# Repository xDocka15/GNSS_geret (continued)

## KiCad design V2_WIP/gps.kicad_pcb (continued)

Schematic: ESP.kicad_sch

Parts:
C2, C14, C15: 100nF; C_0603_1608Metric_Pad1.08x0.95mm_HandSolder
C3, C11, C204: 10uF; C_0603_1608Metric_Pad1.08x0.95mm_HandSolder
C201: 22uF; C_0603_1608Metric_Pad1.08x0.95mm_HandSolder
C202: 470uF; C_Elec_6.3x7.7; not fitted
C203: 1uF; C_0603_1608Metric_Pad1.08x0.95mm_HandSolder
D3, D4: M2; D_SMA
D6, D7: 1N4148W-G3-08; D_SOD-123
D201: LED; LED_D3.0mm
J202: USB4145-03-0230-C; USB4145030230C; Manufacturer_Part_Number USB4145-03-0230-C
Q1: IRLML5203; SOT-23
Q2, Q3: S8050; SOT-23-3
R2, R15: 220; R_0603_1608Metric_Pad0.98x0.95mm_HandSolder
R9, R12, R20, R203: 10k; R_0603_1608Metric_Pad0.98x0.95mm_HandSolder
R10, R16: 2k; R_0603_1608Metric_Pad0.98x0.95mm_HandSolder
R11: 200k; R_0603_1608Metric_Pad0.98x0.95mm_HandSolder
R108: 1k; R_0603_1608Metric_Pad0.98x0.95mm_HandSolder
R202: Manual rst; R_0603_1608Metric_Pad0.98x0.95mm_HandSolder; not fitted
R204, R205: 5k1; R_0603_1608Metric_Pad0.98x0.95mm_HandSolder
SW2: PTS647SN70SMTR2N LFS; SW_SPST_PTS647_Sx38
TP8: +3V3_ESP; TestPoint_Pad_D1.0mm
TP201: FLED; TestPoint_Pad_D1.0mm
TP202: LDO_VCC; TestPoint_Pad_D1.0mm
U1: ESP32-WROOM-32UE
U14: *CH340K; SSOP-10-1EP_3.9x4.9mm_P1mm_EP2.1x3.3mm
U201: RT9080-33GJ5; SOT-23-5_HandSoldering

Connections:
+3V3_ESP: C2.1, C3.1, C201.1, C202.1, C203.1, C204.1, R9.1, R108.2, R203.1, TP8.1 (1_1), U1.2 (VDD), U201.5 (VOUT); also elsewhere on the board
/CLK: U1.11 (IO26); also elsewhere on the board
/DT: U1.12 (IO27); also elsewhere on the board
/ESP/DTR: Q3.1 (E), R20.2, U14.4 (~DTR)
/ESP/D_N: J202.A7 (DN1), J202.B7 (DN2), U14.2 (UD-)
/ESP/D_P: J202.A6 (DP1), J202.B6 (DP2), U14.1 (UD+)
/ESP/IO0: D7.2 (A), U1.25 (IO0)
/ESP/IO2: R10.1, TP201.1 (1_1), U1.24 (IO2)
/ESP/IO12: U1.14 (IO12); also elsewhere on the board
/ESP/IO15: R2.1, U1.23 (IO15)
/ESP/RST: D6.2 (A), R9.2, R202.1, U1.3 (EN)
/ESP/RTS: Q2.1 (E), Q3.2 (B), U14.6 (~RTS)
/ESP/RxD0: U1.34 (RXD0/IO3), U14.9 (RXD)
/ESP/TxD0: R15.1, U1.35 (TXD0/IO1)
/ESP/VCC: C11.1, D3.1 (K), D4.1 (K), Q1.2 (S), R11.1, TP202.1 (1_1), U201.1 (VIN)
/GNSS_RxD: U1.28 (IO17); also elsewhere on the board
/GNSS_TxD: U1.27 (IO16); also elsewhere on the board
/LDO_EN: U1.9 (IO33); also elsewhere on the board
/LIGHT_SENS: U1.7 (IO35); also elsewhere on the board
/MISO: U1.31 (IO19); also elsewhere on the board
/MOSI: U1.37 (IO23); also elsewhere on the board
/Pulse: U1.13 (IO14); also elsewhere on the board
/RGB_DATA: U1.16 (IO13); also elsewhere on the board
/SCK: U1.30 (IO18); also elsewhere on the board
/SCL_3V3: U1.36 (IO22); also elsewhere on the board
/SDA_3V3: U1.33 (IO21); also elsewhere on the board
/SEL_FL: U1.26 (IO4); also elsewhere on the board
/SEL_IMU: U1.8 (IO32); also elsewhere on the board
/SW: U1.10 (IO25); also elsewhere on the board
/VBATT: Q1.3 (D); also elsewhere on the board
/VUSB: C14.1, D3.2 (A), D4.2 (A), J202.A4 (VBUS_1), J202.A9 (VBUS_2), J202.B4 (VBUS_3), J202.B9 (VBUS_4), Q1.1 (G), R12.2, U14.7 (VCC); also elsewhere on the board
GND: C2.2, C3.2, C11.2, C14.2, C15.2, C201.2, C202.2, C203.2, C204.2, D201.1 (K), J202.A1 (GND_1), J202.A8 (SBU1), J202.A12 (GND_2), J202.B1 (GND_3), J202.B8 (SBU2), J202.B12 (GND_4), J202.MH1 (MH5), J202.MH2 (MH6), J202.MH3, J202.MH4, R12.1, R202.2, R204.2, R205.1, SW2.2, U1.1 (GND), U1.15 (GND), U1.38 (GND), U1.39 (GND), U14.3 (GND), U14.11 (GND), U201.2 (GND); also elsewhere on the board
unnamed: D6.1 (K), Q2.3 (C)
unnamed: D7.1 (K), Q3.3 (C)
unnamed: D201.2 (A), R10.2
unnamed: J202.A5 (CC1), R204.1
unnamed: J202.B5 (CC2), R205.2
unnamed: Q2.2 (B), R20.1
unnamed: R2.2, R203.2, SW2.1
unnamed: R108.1, U1.29 (IO5)
unnamed: R15.2, R16.2, U14.8 (TXD)
unnamed: C15.1, R16.1, U14.10 (V3)
unnamed: R11.2, U201.3 (EN)

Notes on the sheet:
LDO_EN
ENC CLK
SEL_IMU
RTS
SCK MISO SDA SCL MOSI
ENC DT
GNSS TX
PULSE
LIGHT_SENS
RGB_DATA
SEL_FL
TP12
SW2
ENC SW
IMU_INT
GNSSRX
LED
https://www.tme.eu/cz/details/usb4145-03-0230-c/konektory-usb-a-ieee1394/gct/
MaxOut 600mA
Manual rst possible by shorting R202
Pins GPIO6 to GPIO11 are connected to the integrated SPI flash integrated on the module and are not recommended for other uses. IO5, 14, 15 are active HIGH at boot IO0, 5, 15 must be HI at boot IO2, 12 must be LO at boot

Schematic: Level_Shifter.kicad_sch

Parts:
C10: 100nF; C_0603_1608Metric_Pad1.08x0.95mm_HandSolder
R3, R4, R5, R6: 10k; R_0603_1608Metric_Pad0.98x0.95mm_HandSolder
RS1: 200k; R_0603_1608Metric_Pad0.98x0.95mm_HandSolder
U9: *TCA39306DDFR; SOT-23-8

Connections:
+3V3: R3.1, R4.1, U9.2 (VREF1); also elsewhere on the board
+5V: R5.1, R6.1, RS1.1; also elsewhere on the board
/SCL_3V3: R3.2, U9.3 (SCL1); also elsewhere on the board
/SCL_5V: R6.2, U9.6 (SCL2); also elsewhere on the board
/SDA_3V3: R4.2, U9.4 (SDA1); also elsewhere on the board
/SDA_5V: R5.2, U9.5 (SDA2); also elsewhere on the board
GND: C10.1, U9.1 (GND); also elsewhere on the board
unnamed: C10.2, RS1.2, U9.7 (VREF2), U9.8 (EN)

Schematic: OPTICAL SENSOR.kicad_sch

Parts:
C107: 100nF; C_0603_1608Metric_Pad1.08x0.95mm_HandSolder
IC1: OPT3001DNPR; SON65P200X200X65-7N-D; Mouser Part Number 595-OPT3001DNPR
R7, R8: 10k; R_0603_1608Metric_Pad0.98x0.95mm_HandSolder
TP14: OPT_INT; TestPoint_Pad_D1.0mm

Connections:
+3V3: C107.2, IC1.1 (VDD), R7.1, R8.1; also elsewhere on the board
/SCL_3V3: IC1.4 (SCL), R8.2; also elsewhere on the board
/SDA_3V3: IC1.6 (SDA), R7.2; also elsewhere on the board
GND: C107.1, IC1.2 (ADDR), IC1.3 (GND), IC1.7 (EP); also elsewhere on the board
unnamed: IC1.5 (INT), TP14.1 (1_1)

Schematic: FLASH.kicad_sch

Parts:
C101: 100nF; C_0603_1608Metric_Pad1.08x0.95mm_HandSolder
R_E101, R_E102: 10k; R_0603_1608Metric_Pad0.98x0.95mm_HandSolder
U102: W25N02KVZEIR; WSON-8-1EP_8x6mm_P1.27mm_EP3.4x4.3mm

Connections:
+3V3: C101.2, R_E101.1, R_E102.2, U102.8 (VCC); also elsewhere on the board
/MISO: U102.2 (DO(IO1)); also elsewhere on the board
/MOSI: U102.5 (DI(IO0)); also elsewhere on the board
/SCK: U102.6 (CLK); also elsewhere on the board
/SEL_FL: U102.1 (~CS); also elsewhere on the board
GND: C101.1, U102.4 (GND); also elsewhere on the board
unnamed: R_E102.1, U102.3 (IO2)
unnamed: R_E101.2, U102.7 (IO3)

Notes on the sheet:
connected to ESP or PULL UP

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
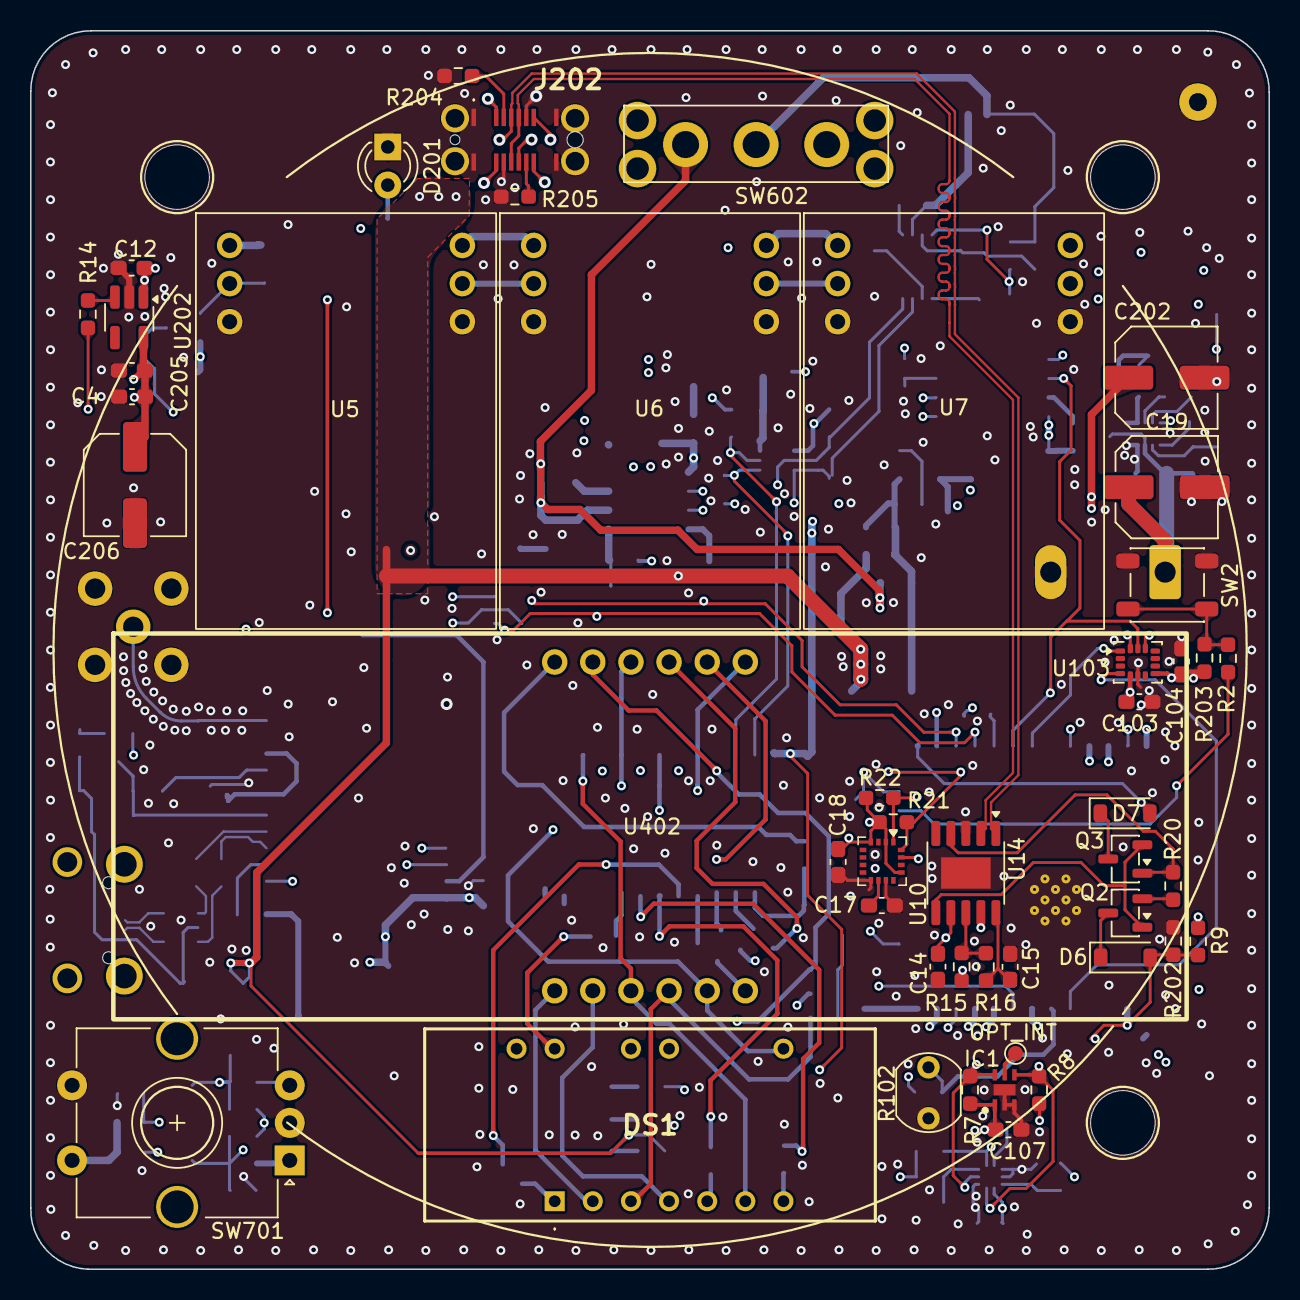
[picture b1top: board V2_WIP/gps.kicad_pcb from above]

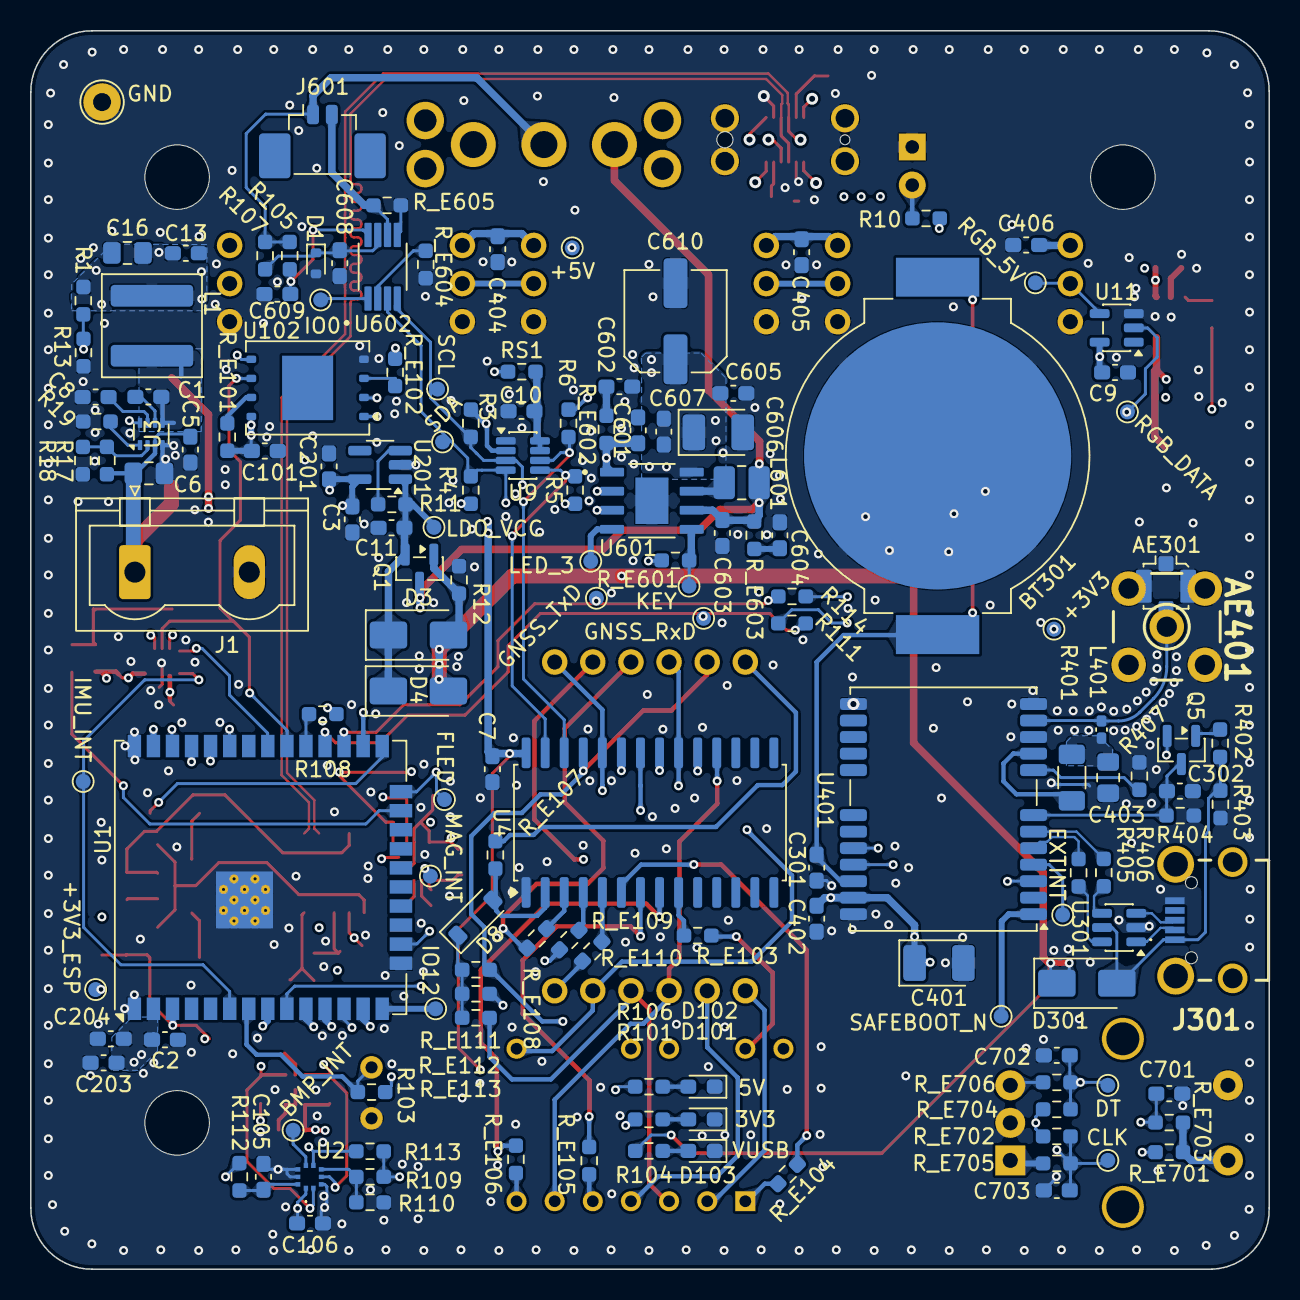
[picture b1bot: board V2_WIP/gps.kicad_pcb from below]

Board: 6 copper layers, 82.5 x 82.5 mm, 198 parts (150 on the bottom side), 129 nets.

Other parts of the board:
C607: 22u; C_0603_1608Metric_Pad1.08x0.95mm_HandSolder

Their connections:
+5V: C607.1, C607.2; also elsewhere on the board

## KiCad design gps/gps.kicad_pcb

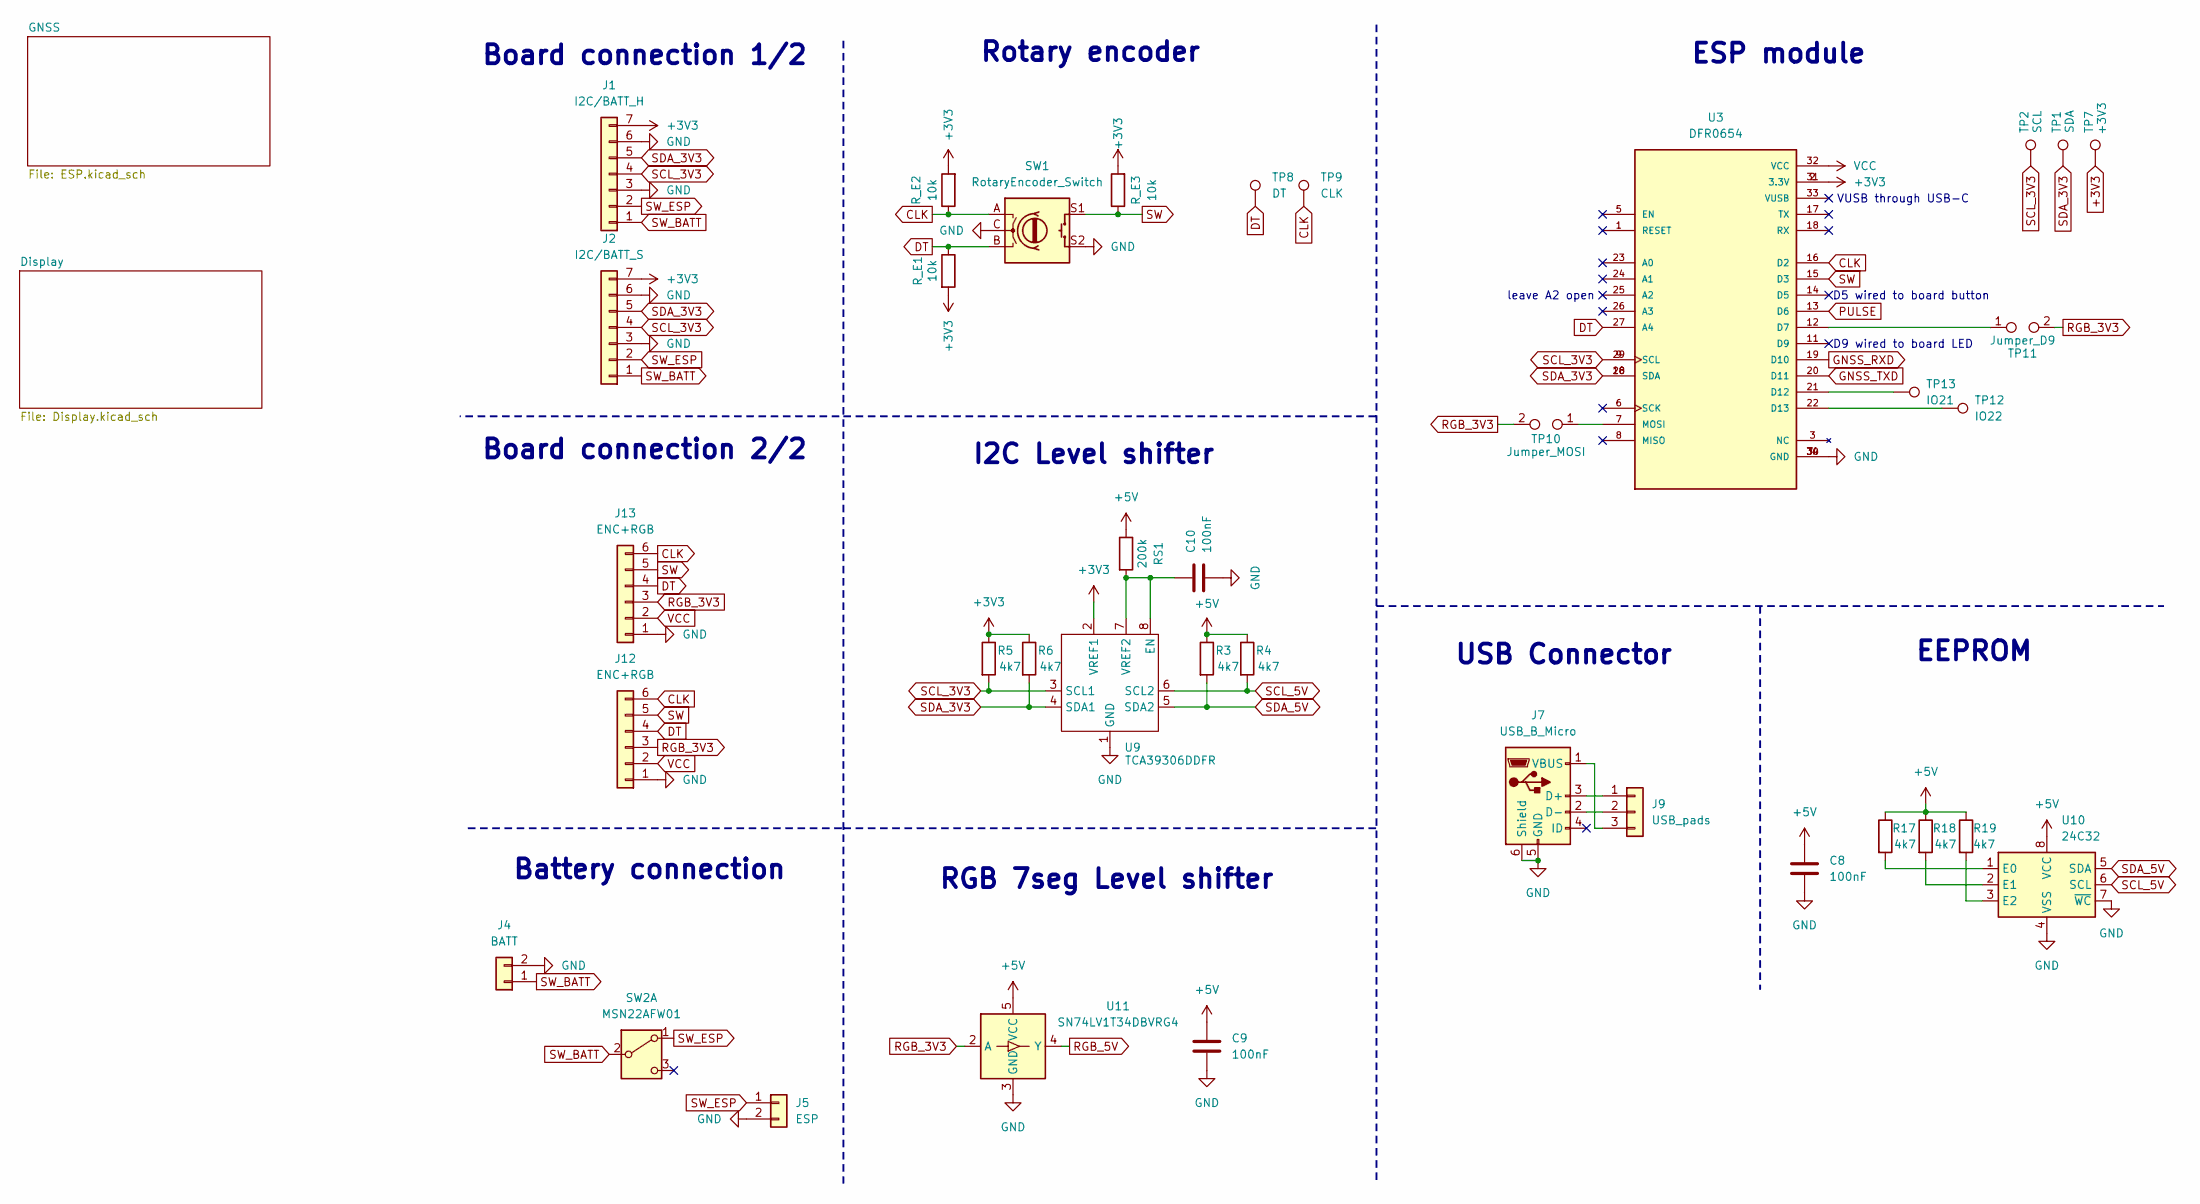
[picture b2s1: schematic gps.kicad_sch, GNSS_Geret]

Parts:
C8, C9, C10: 100nF; C_0805_2012Metric_Pad1.18x1.45mm_HandSolder
J1: I2C/BATT_H; PinHeader_1x07_P2.54mm_Vertical
J2: I2C/BATT_S; PinSocket_1x07_P2.54mm_Vertical
J4: BATT; 1769
J5: ESP; PinSocket_1x02_P2.54mm_Vertical
J7: USB_B_Micro; USB3145301A
J9: USB_pads; PinSocket_1x03_P2.54mm_Vertical
J12: ENC+RGB; PinSocket_1x06_P2.54mm_Vertical
J13: ENC+RGB; PinHeader_1x06_P2.54mm_Vertical
R3, R4, R5, R6, R17, R18, R19: 4k7; R_0805_2012Metric_Pad1.20x1.40mm_HandSolder
RS1: 200k; R_0805_2012Metric_Pad1.20x1.40mm_HandSolder
R_E1, R_E2, R_E3: 10k; R_0805_2012Metric_Pad1.20x1.40mm_HandSolder
SW1: RotaryEncoder_Switch; RotaryEncoder_20mm_WO_mount_holes
SW2: MSN22AFW01
TP1: SDA; TestPoint_Loop_D1.80mm_Drill1.0mm_Beaded
TP2: SCL; TestPoint_Loop_D1.80mm_Drill1.0mm_Beaded
TP7: +3V3; TestPoint_Loop_D1.80mm_Drill1.0mm_Beaded
TP8: DT; TestPoint_Loop_D1.80mm_Drill1.0mm_Beaded
TP9: CLK; TestPoint_Loop_D1.80mm_Drill1.0mm_Beaded
TP10: Jumper_MOSI; R_0805_2012Metric_Pad1.20x1.40mm_HandSolder
TP11: Jumper_D9; R_0805_2012Metric_Pad1.20x1.40mm_HandSolder
TP12: IO22; TestPoint_Loop_D1.80mm_Drill1.0mm_Beaded
TP13: IO21; TestPoint_Loop_D1.80mm_Drill1.0mm_Beaded
U3: DFR0654; DFR0654_2
U9: TCA39306DDFR; SOT-23-8
U10: 24C32; SOIC-8_3.9x4.9mm_P1.27mm
U11: SN74LV1T34DBVRG4; SOT-23-5

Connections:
+3V3: J1.7, J2.7, R5.1, R6.1, R_E1.2, R_E2.2, R_E3.2, TP7.1, U3.2 (3.3V), U3.31 (3.3V), U9.2 (VREF1); also elsewhere on the board
+5V: C8.2, C9.2, R3.1, R4.1, R17.1, R18.1, R19.1, RS1.1, U10.8 (VCC), U11.5 (VCC); also elsewhere on the board
CLK: J12.6, J13.6, R_E2.1, SW1.A, TP9.1, U3.16 (D2)
DT: J12.4, J13.4, R_E1.1, SW1.B, TP8.1, U3.27 (A4)
GND: C8.1, C9.1, C10.1, J1.3, J1.6, J2.3, J2.6, J4.2, J5.2, J7.5 (GND), J7.6 (Shield), J12.1, J13.1, SW1.C, SW1.S2, U3.4 (GND), U3.30 (GND), U3.34 (GND), U9.1 (GND), U10.4 (VSS), U10.7 (~WC), U11.3 (GND); also elsewhere on the board
GNSS_RXD: U3.19 (D10); also elsewhere on the board
GNSS_TXD: U3.20 (D11); also elsewhere on the board
unnamed: J7.3 (D+), J9.1
unnamed: J7.2 (D-), J9.2
unnamed: J7.1 (VBUS), J9.3
unnamed: TP11.1, U3.12 (D7)
unnamed: TP13.1, U3.21 (D12)
unnamed: TP12.1, U3.22 (D13)
unnamed: TP10.1, U3.7 (MOSI)
unnamed: C10.2, RS1.2, U9.7 (VREF2), U9.8 (EN)
unnamed: R17.2, U10.1 (E0)
unnamed: R18.2, U10.2 (E1)
unnamed: R19.2, U10.3 (E2)
PULSE: U3.13 (D6); also elsewhere on the board
RGB_3V3: J12.3, J13.3, TP10.2, TP11.2, U11.2 (A); also elsewhere on the board
RGB_5V: U11.4 (Y); also elsewhere on the board
SCL_3V3: J1.4, J2.4, R5.2, TP2.1, U3.9 (SCL), U3.29 (SCL), U9.3 (SCL1)
SCL_5V: R4.2, U9.6 (SCL2), U10.6 (SCL); also elsewhere on the board
SDA_3V3: J1.5, J2.5, R6.2, TP1.1, U3.10 (SDA), U3.28 (SDA), U9.4 (SDA1)
SDA_5V: R3.2, U9.5 (SDA2), U10.5 (SDA); also elsewhere on the board
SW: J12.5, J13.5, R_E3.1, SW1.S1, U3.15 (D3)
SW_BATT: J1.1, J2.1, J4.1, SW2.2 (B)
SW_ESP: J1.2, J2.2, J5.1, SW2.1 (A)
VCC: J12.2, J13.2, U3.32 (VCC); also elsewhere on the board

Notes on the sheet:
ESP module
D9 wired to board LED
EEPROM
RGB 7seg Level shifter
VUSB through USB-C
USB Connector
D5 wired to board button
Board connection 2/2
Battery connection
leave A2 open
I2C Level shifter
Rotary encoder
Board connection 1/2

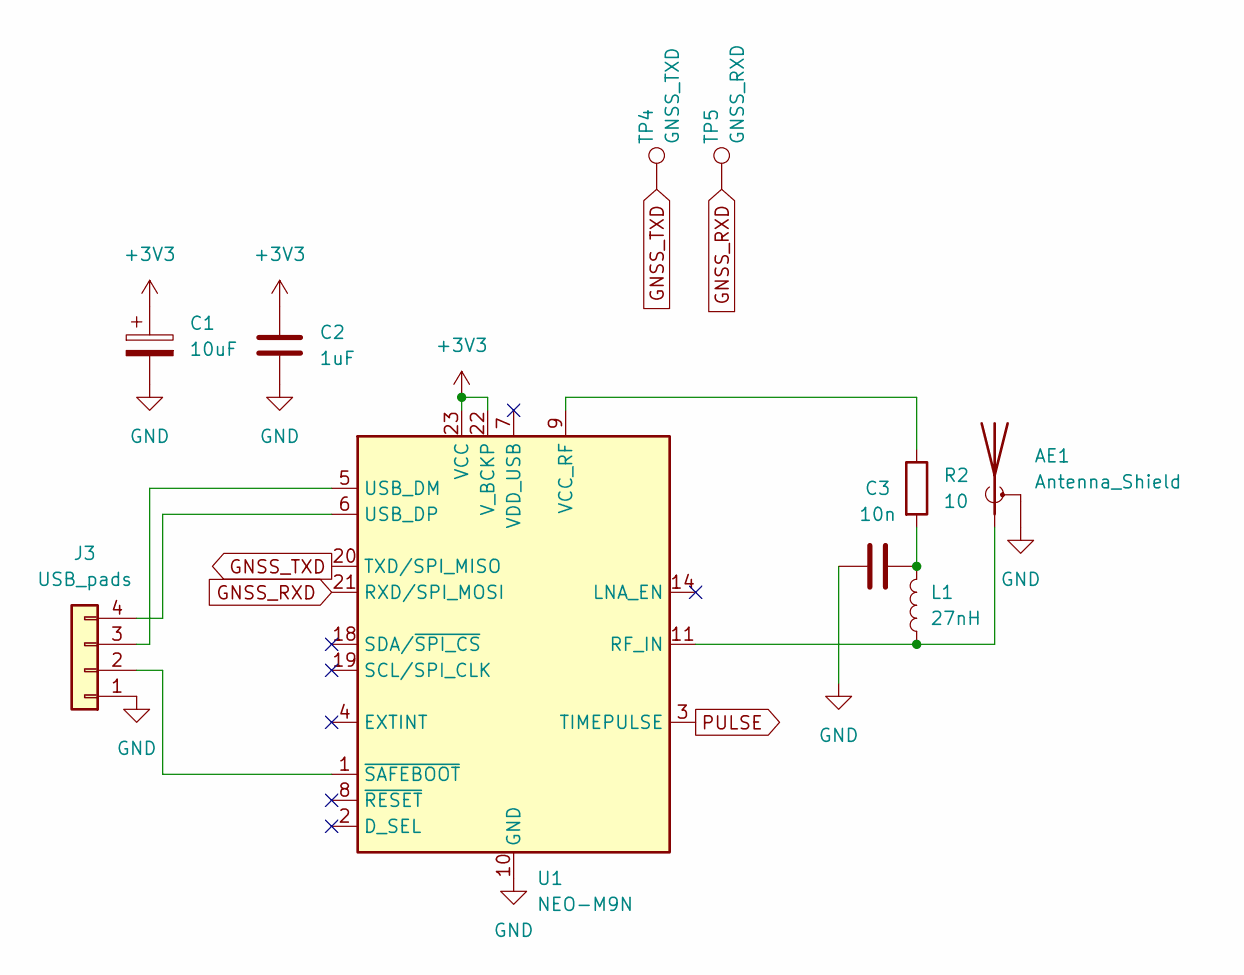
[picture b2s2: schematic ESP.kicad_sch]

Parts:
AE1: Antenna_Shield; lemo_epb00250ntn
C1: 10uF; CP_EIA-3528-15_AVX-H_Pad1.50x2.35mm_HandSolder
C2: 1uF; C_0603_1608Metric_Pad1.08x0.95mm_HandSolder
C3: 10n; C_0805_2012Metric_Pad1.18x1.45mm_HandSolder
J3: USB_pads; PinHeader_1x04_P2.54mm_Vertical
L1: 27nH; L_0402_1005Metric_Pad0.77x0.64mm_HandSolder
R2: 10; R_1206_3216Metric_Pad1.30x1.75mm_HandSolder
TP4: GNSS_TXD; TestPoint_Loop_D1.80mm_Drill1.0mm_Beaded
TP5: GNSS_RXD; TestPoint_Loop_D1.80mm_Drill1.0mm_Beaded
U1: NEO-M9N; ublox_NEO

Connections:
+3V3: C1.1, C2.1, U1.22 (V_BCKP), U1.23 (VCC); also elsewhere on the board
GND: AE1.2 (Shield), C1.2, C2.2, C3.1, J3.1, U1.10 (GND), U1.12 (GND), U1.13 (GND), U1.24 (GND); also elsewhere on the board
GNSS_RXD: TP5.1, U1.21 (RXD/SPI_MOSI); also elsewhere on the board
GNSS_TXD: TP4.1, U1.20 (TXD/SPI_MISO); also elsewhere on the board
unnamed: AE1.1 (A), L1.1, U1.11 (RF_IN)
unnamed: C3.2, L1.2, R2.2
unnamed: J3.2, U1.1 (~SAFEBOOT)
unnamed: J3.3, U1.5 (USB_DM)
unnamed: J3.4, U1.6 (USB_DP)
unnamed: R2.1, U1.9 (VCC_RF)
PULSE: U1.3 (TIMEPULSE); also elsewhere on the board

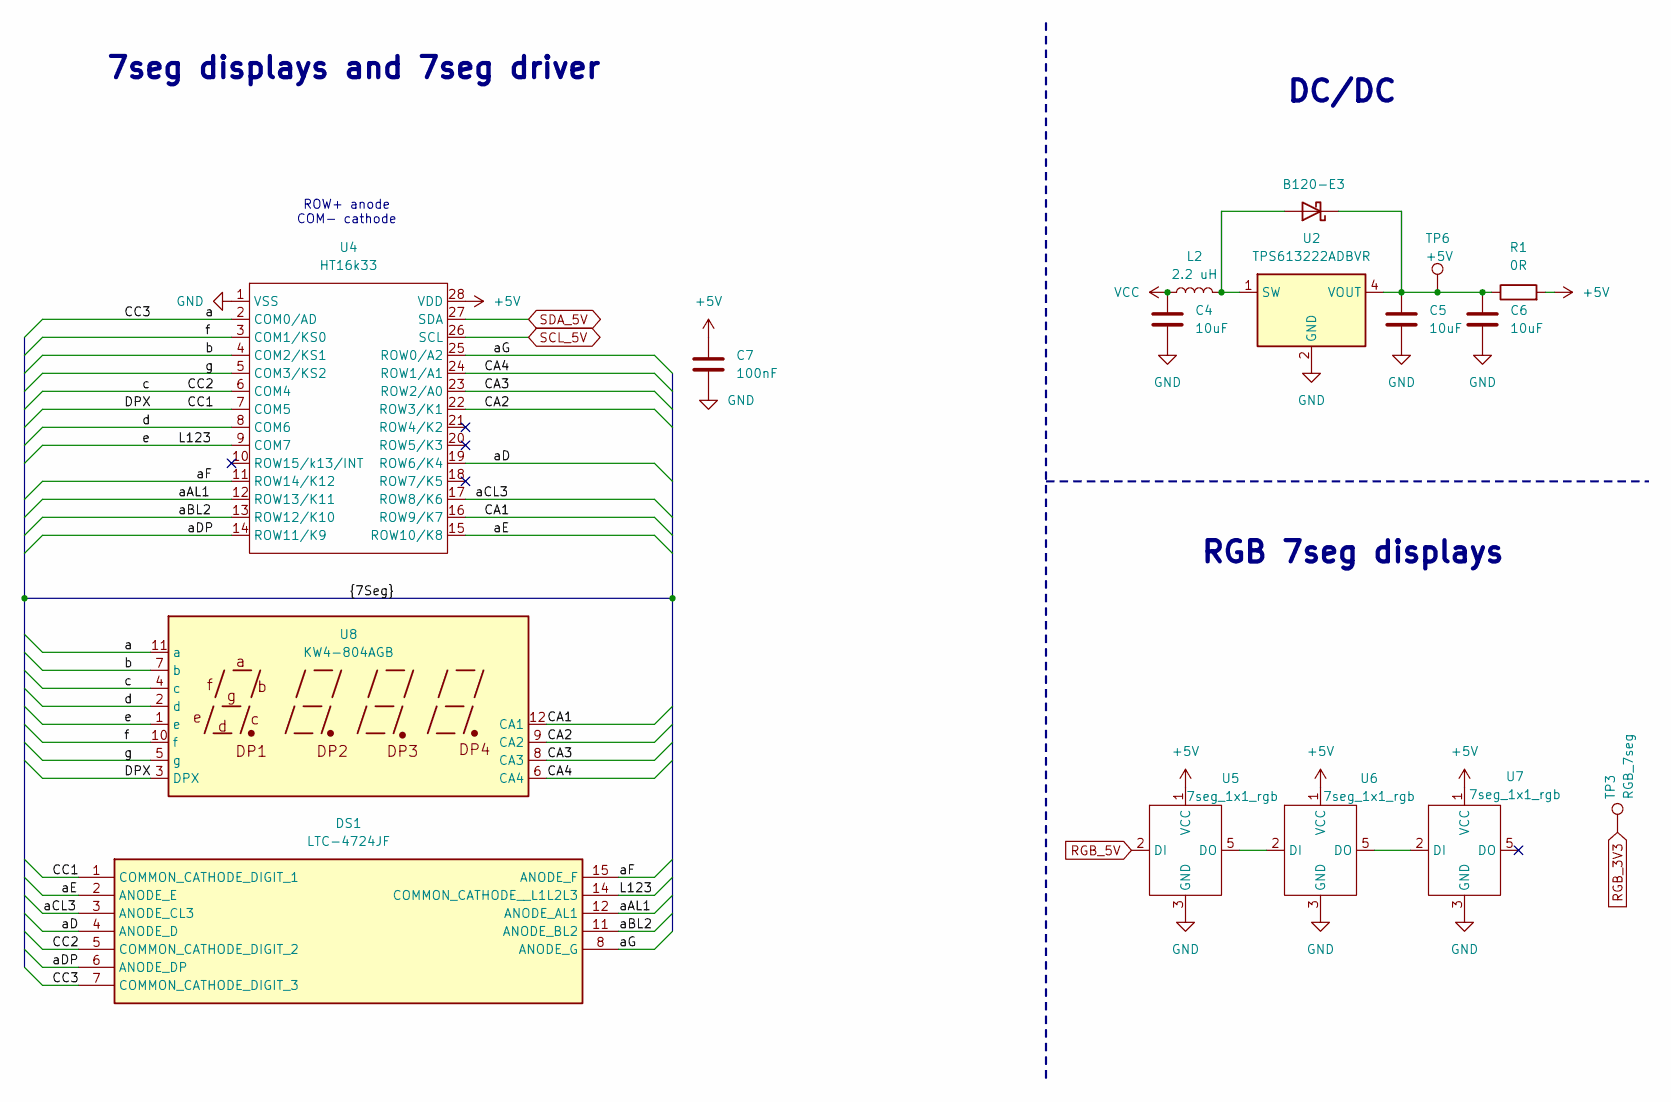
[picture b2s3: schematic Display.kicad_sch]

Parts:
C4, C5, C6: 10uF; C_0603_1608Metric_Pad1.08x0.95mm_HandSolder
C7: 100nF; C_0805_2012Metric_Pad1.18x1.45mm_HandSolder
D2: B120-E3; D_SMA
DS1: LTC-4724JF; LTC4724JF; Mouser Part Number 859-LTC-4724JF
L2: 2.2 uH; L_1008_2520Metric_Pad1.43x2.20mm_HandSolder
R1: 0R; R_0805_2012Metric_Pad1.20x1.40mm_HandSolder
TP3: RGB_7seg; TestPoint_Loop_D1.80mm_Drill1.0mm_Beaded
TP6: +5V; TestPoint_Loop_D1.80mm_Drill1.0mm_Beaded
U2: TPS613222ADBVR; SOT-23-5
U4: HT16k33; soic-28
U5, U6, U7: 7seg_1x1_rgb
U8: KW4-804AGB; 7seg_4x1

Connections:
+5V: C7.1, R1.2, U4.28 (VDD), U5.1 (VCC), U6.1 (VCC), U7.1 (VCC); also elsewhere on the board
/Display/CA1: U4.16 (ROW9/K7), U8.12 (CA1)
/Display/CA2: U4.22 (ROW3/K1), U8.9 (CA2)
/Display/CA3: U4.23 (ROW2/A0), U8.8 (CA3)
/Display/CA4: U4.24 (ROW1/A1), U8.6 (CA4)
/Display/CC1: DS1.1 (COMMON_CATHODE_DIGIT_1), U4.7 (COM5), U8.3 (DPX)
/Display/CC2: DS1.5 (COMMON_CATHODE_DIGIT_2), U4.6 (COM4), U8.4 (c)
/Display/CC3: DS1.7 (COMMON_CATHODE_DIGIT_3), U4.2 (COM0/AD), U8.11 (a)
/Display/L123: DS1.14 (COMMON_CATHODE__L1L2L3), U4.9 (COM7), U8.1 (e)
/Display/aAL1: DS1.12 (ANODE_AL1), U4.12 (ROW13/K11)
/Display/aBL2: DS1.11 (ANODE_BL2), U4.13 (ROW12/K10)
/Display/aCL3: DS1.3 (ANODE_CL3), U4.17 (ROW8/K6)
/Display/aD: DS1.4 (ANODE_D), U4.19 (ROW6/K4)
/Display/aDP: DS1.6 (ANODE_DP), U4.14 (ROW11/K9)
/Display/aE: DS1.2 (ANODE_E), U4.15 (ROW10/K8)
/Display/aF: DS1.15 (ANODE_F), U4.11 (ROW14/K12)
/Display/aG: DS1.8 (ANODE_G), U4.25 (ROW0/A2)
/Display/b: U4.4 (COM2/KS1), U8.7 (b)
/Display/d: U4.8 (COM6), U8.2 (d)
/Display/f: U4.3 (COM1/KS0), U8.10 (f)
/Display/g: U4.5 (COM3/KS2), U8.5 (g)
GND: C4.2, C5.2, C6.2, C7.2, U2.2 (GND), U4.1 (VSS), U5.3 (GND), U6.3 (GND), U7.3 (GND); also elsewhere on the board
unnamed: D2.2 (A), L2.2, U2.1 (SW)
unnamed: C5.1, C6.1, D2.1 (K), R1.1, TP6.1, U2.4 (VOUT)
unnamed: U5.5 (DO), U6.2 (DI)
unnamed: U6.5 (DO), U7.2 (DI)
RGB_3V3: TP3.1; also elsewhere on the board
RGB_5V: U5.2 (DI); also elsewhere on the board
SCL_5V: U4.26 (SCL); also elsewhere on the board
SDA_5V: U4.27 (SDA); also elsewhere on the board
VCC: C4.1, L2.1; also elsewhere on the board

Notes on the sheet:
RGB 7seg displays
7seg displays and 7seg driver
ROW+ anode COM- cathode
DC/DC

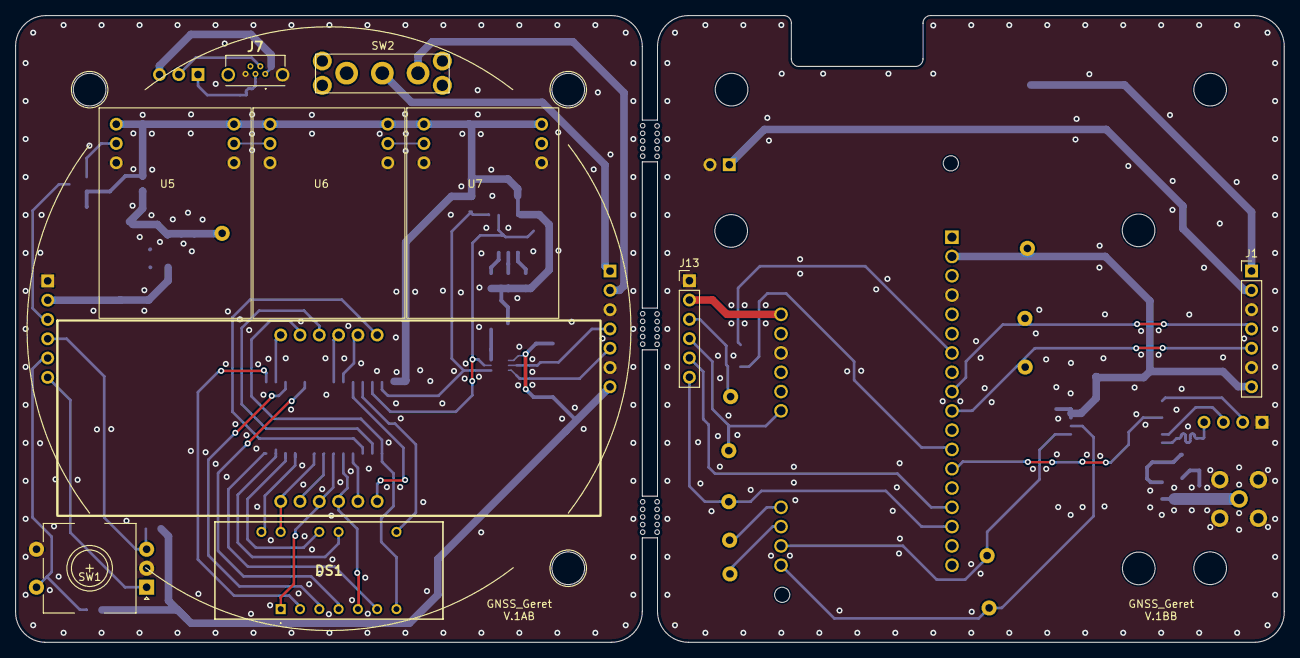
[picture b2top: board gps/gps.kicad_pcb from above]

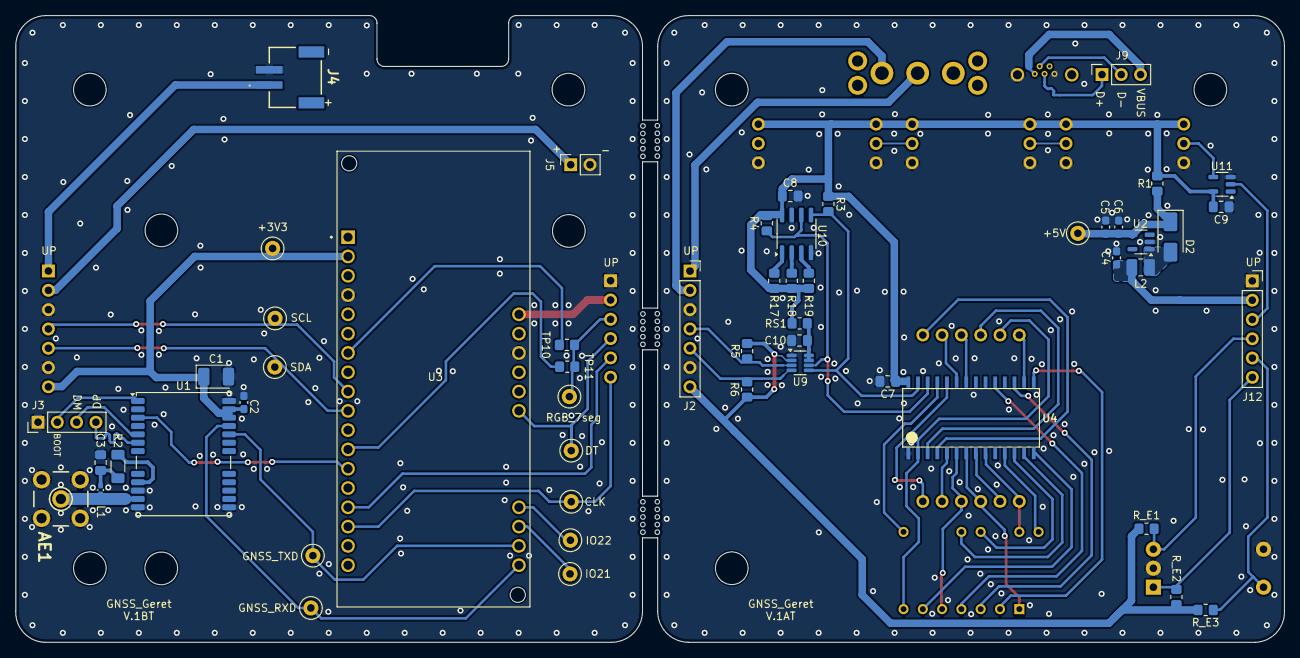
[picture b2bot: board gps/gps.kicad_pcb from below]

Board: 2 copper layers, 167.0 x 82.5 mm, 63 parts (53 on the bottom side), 59 nets.

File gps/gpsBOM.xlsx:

Reference | Value | Datasheet | Footprint | Qty | DNP
C1,C4,C5,C6 | 10uF | ~ | -- mixed values -- | 4
C2 | 1uF | ~ | Capacitor_SMD:C_0603_1608Metric_Pad1.08x0.95mm_HandSolder | 1
C3 | 10n | ~ | Capacitor_SMD:C_0805_2012Metric_Pad1.18x1.45mm_HandSolder | 1
C7,C8 | 100nF | ~ | Capacitor_SMD:C_0805_2012Metric_Pad1.18x1.45mm_HandSolder | 2
D2 | B120-E3 |  | Diode_SMD:D_SMA | 1
DS1 | LTC-4724JF | https://media.digikey.com/pdf/Data%20Sheets/Lite-On%20PDFs/L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 | Display_7Segment:LTC4724JF | 1
J3,J9 | USB_pads | ~ | -- mixed values -- | 2
J4 | BATT | ~ | 1769:1769 | 1
J7 | USB_B_Micro | ~ | Connector_USB:USB_Mini-B_Tensility_54-00023_Vertical_CircularHoles | 1
J12,J13 | ENC+RGB | ~ | -- mixed values -- | 2
L1 | 27nH | ~ | Inductor_SMD:L_0402_1005Metric_Pad0.77x0.64mm_HandSolder | 1
L2 | 2.2 uH | ~ | Inductor_SMD:L_1008_2520Metric_Pad1.43x2.20mm_HandSolder | 1
R1 | 0R | ~ | Resistor_SMD:R_0805_2012Metric_Pad1.20x1.40mm_HandSolder | 1
R2 | 10 | ~ | Resistor_SMD:R_1206_3216Metric_Pad1.30x1.75mm_HandSolder | 1
R11,R12,R17,R18,R19 | 4k7 | ~ | Resistor_SMD:R_0805_2012Metric_Pad1.20x1.40mm_HandSolder | 5
R_E1,R_E2,R_E3 | 10k | ~ | Resistor_SMD:R_0603_1608Metric_Pad0.98x0.95mm_HandSolder | 3
SW1 | RotaryEncoder_Switch | ~ | Rotary_Encoder:RotaryEncoder_Alps_EC12E-Switch_Vertical_H20mm_CircularMountingH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 | 1
SW2 | SW_DPDT_x2 | ~ | Button_Switch_THT:MSN22AFW01 | 1
TP10 | Jumper_MOSI | ~ | Resistor_SMD:R_0805_2012Metric_Pad1.20x1.40mm_HandSolder | 1
TP11 | Jumper_D9 | ~ | Resistor_SMD:R_0805_2012Metric_Pad1.20x1.40mm_HandSolder | 1
U1 | NEO-M9N |  | RF_GPS:ublox_NEO | 1
U2 | TPS613222ADBVR |  | Package_TO_SOT_SMD:SOT-23-5 | 1
U3 | DFR0654 |  | DFR0654:DFR0654_2 | 1
U4 | HT16k33 |  | w_smd_dil:soic-28 | 1
U5,U6,U7 | 7seg_1x1_rgb |  | 7seg_rgb:7seg_1x1_rgb | 3
U8 | KW4-804AGB |  | 7seg_rgb:7seg_4x1 | 1
U10 | 24C32 |  | Package_SO:SOIC-8_3.9x4.9mm_P1.27mm | 1

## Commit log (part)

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2024-07-19 pcb update
2024-07-19 update pcd/sch
2024-07-19 update pcb/housing
2024-07-25 PCB-update
2024-07-26 PCB-tweaked-BattConn
2024-07-26 test
2024-07-26 tweaks
2024-07-27 changed eeprom > 5V, RF antenna track corrected to 50ohm
2024-07-27 added missing i2c connection
2024-07-27 added level shifters for i2C and RGB displey,
2024-07-27 added pullup for 3V3 i2c
2024-07-28 PCB - adjusted connectors to be inside circle (User.1)
2024-07-28 PCB - reworked mouse-bites
2024-07-28 added gerbers
2024-08-01 Final V1, cleaned display connections
2024-08-04 cleaned schematic
2024-08-04 deleted unnecessary backups
2024-08-05 updated pdf/
2024-08-06 pdf/ added fabs
2024-08-06 updated bom
2024-08-14 added 3D_Print/ with front panel models
2024-08-14 added images, separated 3D_Print/ into folders
2024-08-14 Update README.md
    added image of board
2024-08-15 3D_Print/ added 10.5mm version of front_panel.stl
2024-08-15 3D_Print/ changed 10.5mm version of front_panel.stl to 9.5mm
2024-08-15 3D_Print/ added readme
2024-08-16 /images/ added board4.png; updated /README.md
2024-08-16 updated image positions in /README.md
2025-06-15 -Deleted backups for V1 -Cloned V1 into V2 -V2/ added USB interface for GNSS -V2/ mergo into 1 board -V2/ Switched to a 6 layer board
2025-06-17 minor schematic changes
2025-06-17 switched esp modul symbol for esp sheet
2025-06-19 added LED indicators, light sensor, changed to CC 7seg displays
2025-06-19 added battery monitoring circuits
2025-06-20 added FLASH module; moved encoder into separate schematic
2025-06-21 added USB, button
2025-06-22 fixed errors in schematic
2025-06-22 schematic tweaks
2025-06-29 Removed EEPROM, Adjusted Flash connection, renamed ESP pins and several other signals
2025-07-08 minor changes
2025-08-01 finallizes schematic; pcb progress
2025-08-05 updated most datashets
2026-03-06 up to date i dont remember what changed
